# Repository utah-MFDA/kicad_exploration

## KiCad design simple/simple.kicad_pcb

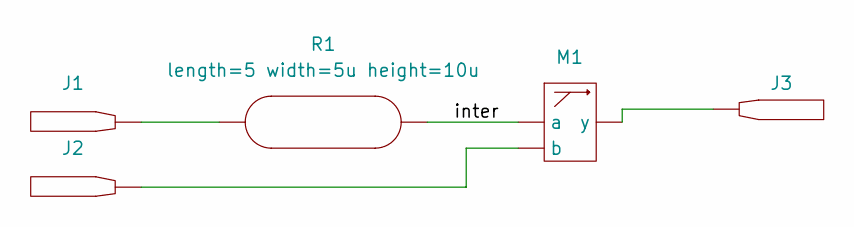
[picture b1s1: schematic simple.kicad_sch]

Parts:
J1, J2, J3: pinhole_325px_0
M1: diffmix_25px_0
R1: length=5 width=5u height=10u; serpentine_50px_0

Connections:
/inter: M1.1 (a), R1.2 (out)
unnamed: J1.1 (connect), R1.1 (in)
unnamed: J2.1 (connect), M1.2 (b_fluid)
unnamed: J3.1 (connect), M1.3 (y)

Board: 2 copper layers, 5 parts (0 on the bottom side), 4 nets.

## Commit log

2024-06-19 Initial test version of symbol library
2024-06-20 Add names and pins back into symbols.
2024-06-20 Add schematic implementation of kinase design.
2024-06-21 Move kinase project to subdirectory
2024-06-21 Add nucleic acid processor example.
2024-06-21 Remove backup archives for kinase
2024-06-24 Spice experiments initial implementation.
2024-06-24 Add spice fluidics project.
